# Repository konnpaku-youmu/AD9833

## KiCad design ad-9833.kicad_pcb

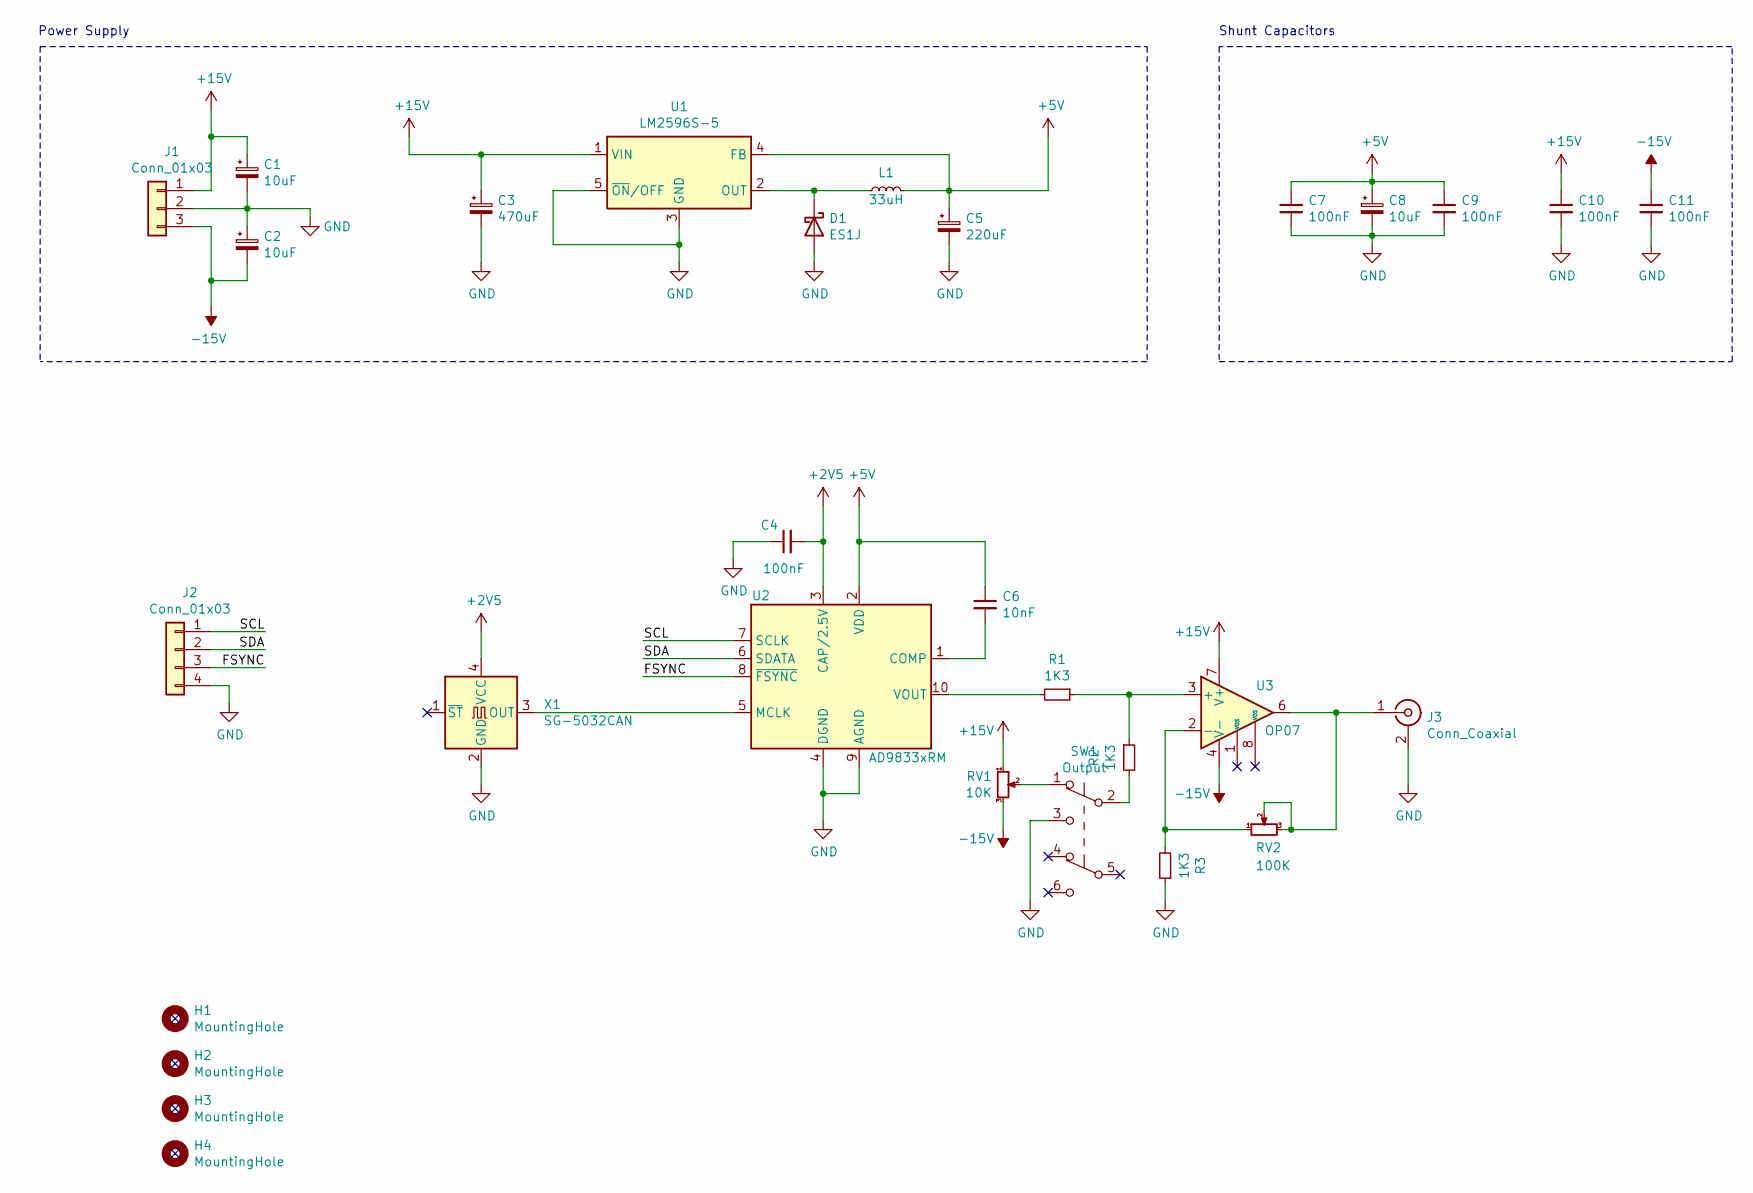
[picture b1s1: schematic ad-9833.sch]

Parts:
C1, C2, C8: 10uF; CP_Elec_5x5.4
C3: 470uF; C_Elec_10x10.2
C4, C7, C9, C10, C11: 100nF; C_0603_1608Metric_Pad1.08x0.95mm_HandSolder
C5: 220uF; C_Elec_8x10.2
C6: 10nF; C_0603_1608Metric_Pad1.08x0.95mm_HandSolder
D1: ES1J; D_SMA_Handsoldering
H1, H2, H3, H4: MountingHole; MountingHole_2.2mm_M2_Pad_Via
J1: Conn_01x03; PinHeader_1x03_P2.54mm_Vertical
J2: Conn_01x03; PinHeader_1x04_P2.54mm_Vertical
J3: Conn_Coaxial; BNC_Amphenol_B6252HB-NPP3G-50_Horizontal
L1: 33uH; L_Taiyo-Yuden_NR-10050_9.8x10.0mm_HandSoldering
R1, R2, R3: 1K3; R_0603_1608Metric_Pad0.98x0.95mm_HandSolder
RV1: 10K; Potentiometer_Vishay_TS53YJ_Vertical
RV2: 100K; Potentiometer_Vishay_TS53YJ_Vertical
SW1: Output; XKB5858-Z
U1: LM2596S-5; TO-263-5_TabPin3
U2: AD9833xRM; MSOP-10_3x3mm_P0.5mm
U3: OP07; SOIC-8_3.9x4.9mm_P1.27mm
X1: SG-5032CAN; Oscillator_SMD_SeikoEpson_SG8002LB-4Pin_5.0x3.2mm_HandSolde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

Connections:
+2V5: C4.2, U2.3 (CAP/2.5V), X1.4 (VCC)
+5V: C5.1, C6.1, C7.1, C8.1, C9.1, L1.2, U1.4 (FB), U2.2 (VDD)
+15V: C1.1, C3.1, C10.1, J1.1, RV1.1, U1.1 (VIN), U3.7 (V+)
-15V: C2.2, C11.1, J1.3, RV1.3, U3.4 (V-)
/FSYNC: J2.3, U2.8 (~FSYNC)
/SCL: J2.1, U2.7 (SCLK)
/SDA: J2.2, U2.6 (SDATA)
GND: C1.2, C2.1, C3.2, C4.1, C5.2, C7.2, C8.2, C9.2, C10.2, C11.2, D1.2 (A), J1.2, J2.4, J3.2 (Ext), R3.1, SW1.3 (C), U1.3 (GND), U1.5 (~ON~/OFF), U2.4 (DGND), U2.9 (AGND), X1.2 (GND)
unnamed: C6.2, U2.1 (COMP)
unnamed: D1.1 (K), L1.1, U1.2 (OUT)
unnamed: J3.1 (In), RV2.2, RV2.3, U3.6
unnamed: R1.1, R2.1, U3.3 (+)
unnamed: R1.2, U2.10 (VOUT)
unnamed: R2.2, SW1.2 (B)
unnamed: R3.2, RV2.1, U3.2 (-)
unnamed: RV1.2, SW1.1 (A)
unnamed: U2.5 (MCLK), X1.3 (OUT)

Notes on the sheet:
Power Supply
Shunt Capacitors

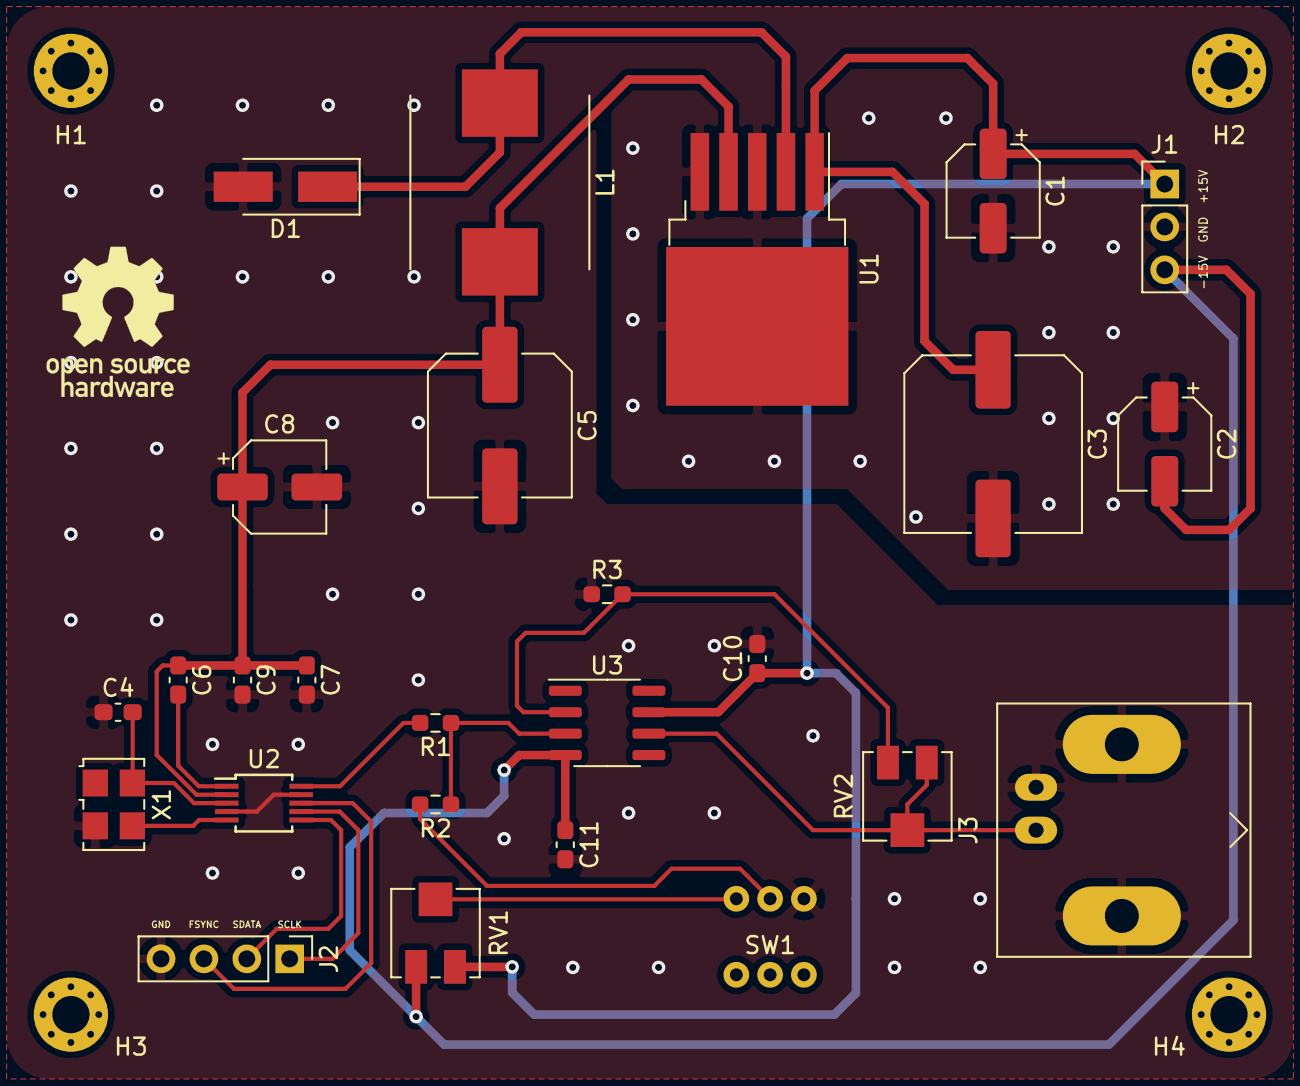
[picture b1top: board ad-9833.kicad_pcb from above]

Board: 2 copper layers, 30 parts (0 on the bottom side), 17 nets.

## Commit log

2021-04-27 version 0
